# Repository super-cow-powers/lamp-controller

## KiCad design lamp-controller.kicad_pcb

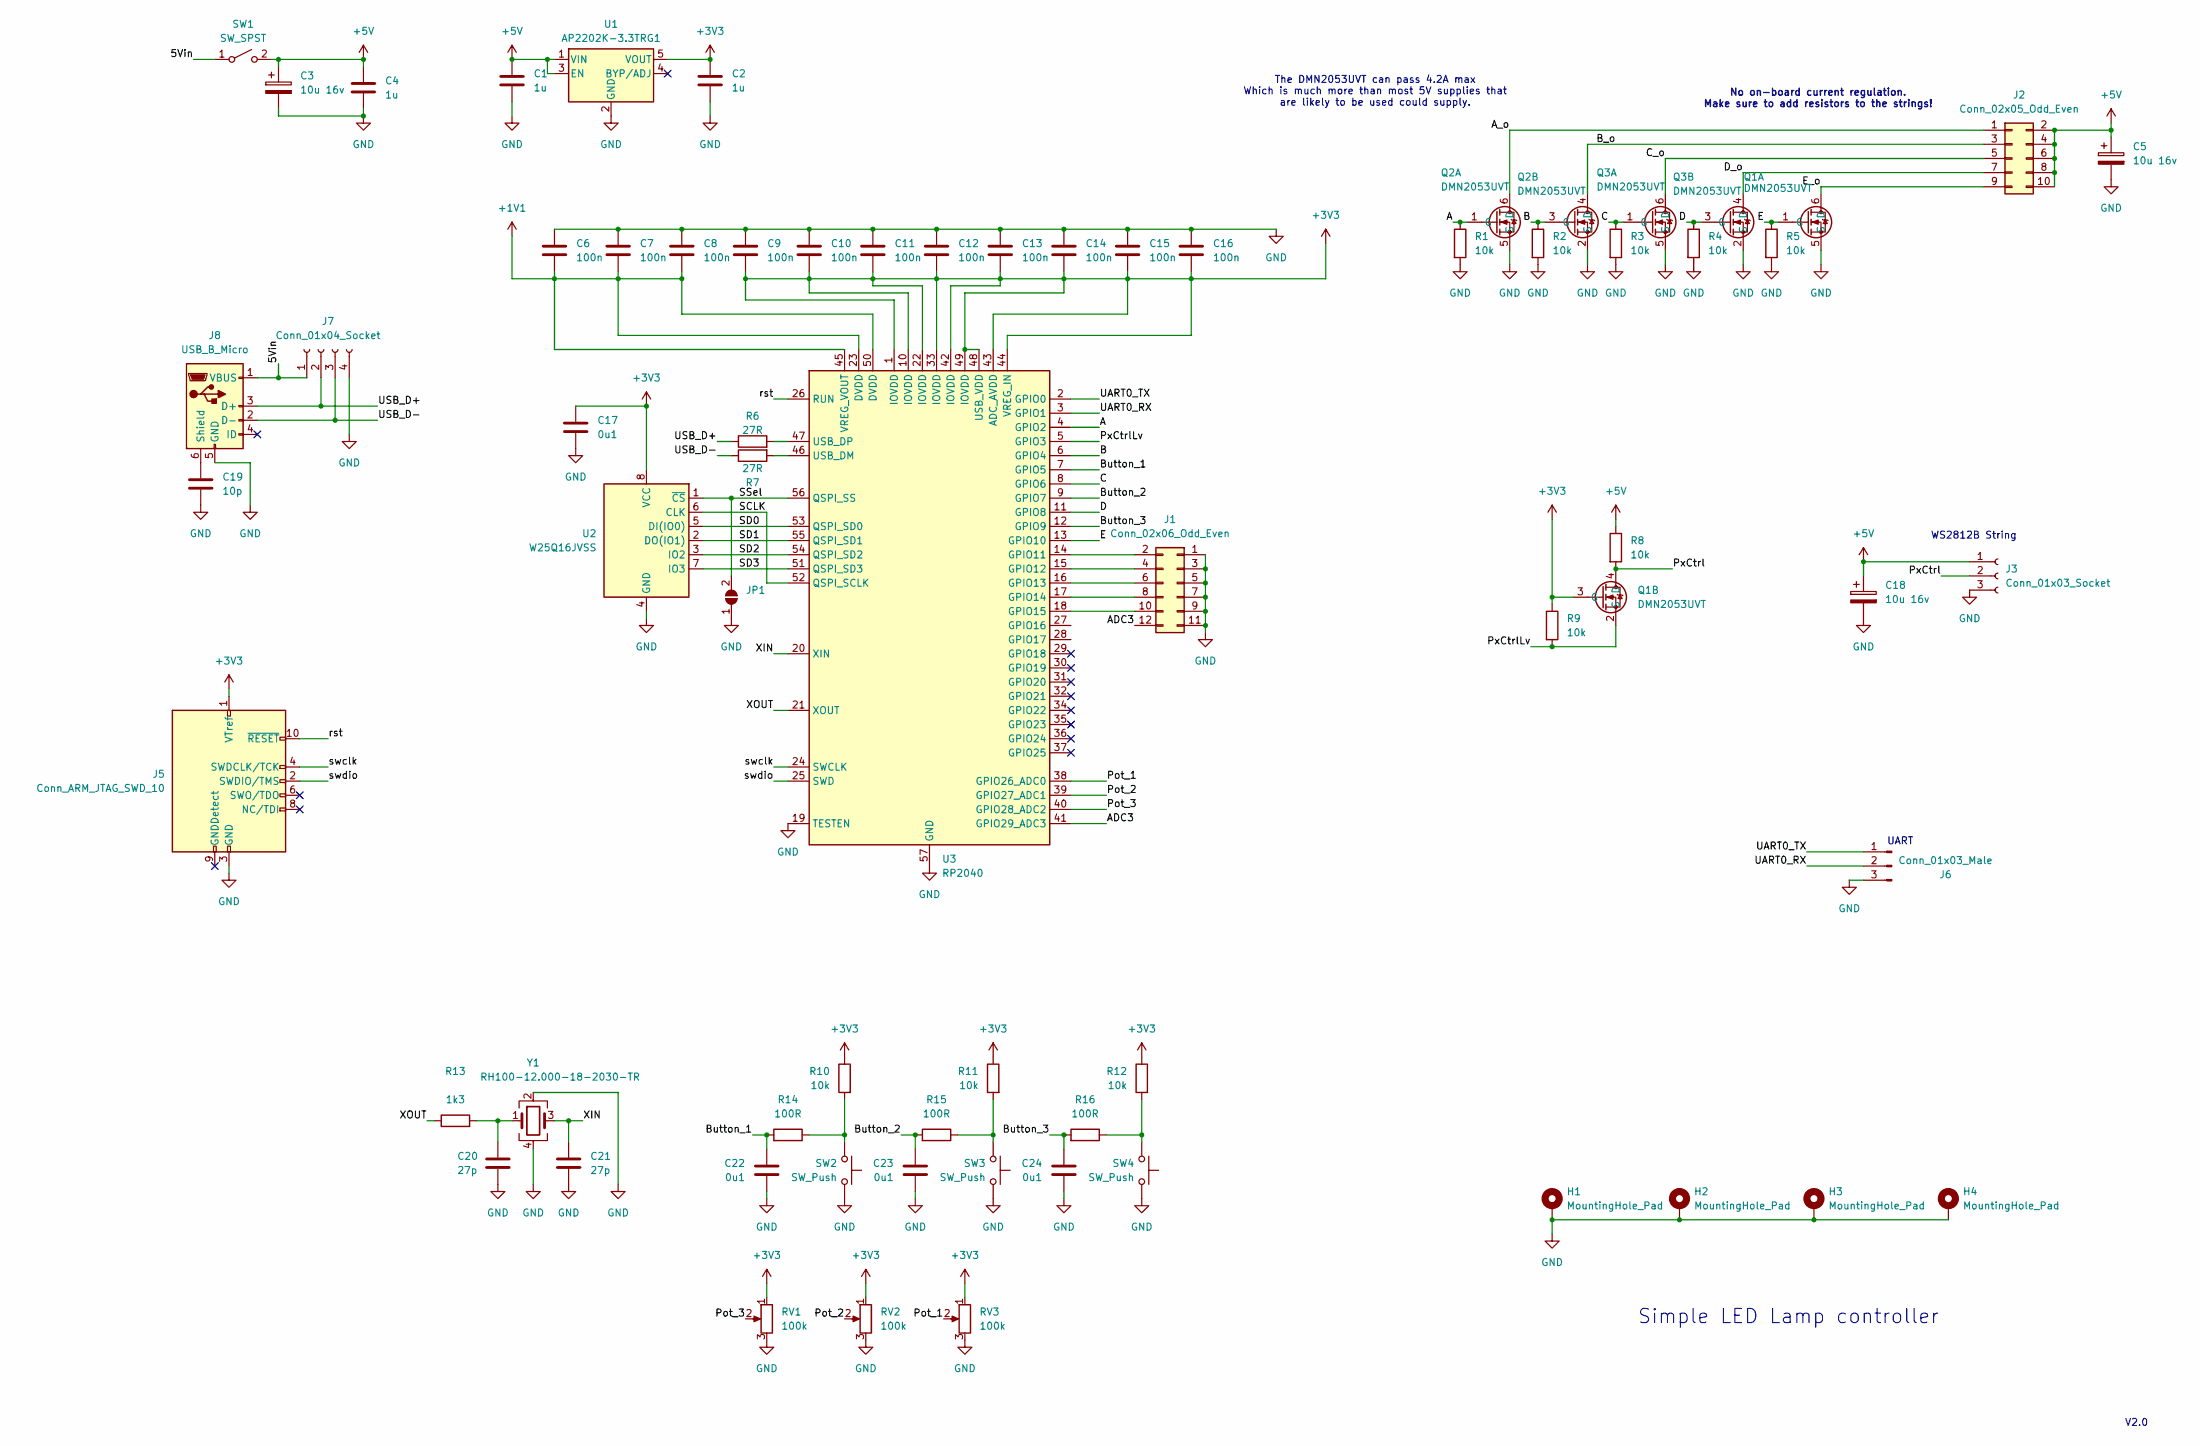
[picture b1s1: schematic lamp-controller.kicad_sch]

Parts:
C1, C2, C4: 1u; C_0603_1608Metric_Pad1.08x0.95mm_HandSolder
C3, C5, C18: 10u 16v; CP_Radial_D4.0mm_P2.00mm
C6, C7, C8, C9, C10, C11, C12, C13, C14, C15, C16: 100n; C_0603_1608Metric_Pad1.08x0.95mm_HandSolder
C17, C22, C23, C24: 0u1; C_0603_1608Metric_Pad1.08x0.95mm_HandSolder
C19: 10p; C_0603_1608Metric_Pad1.08x0.95mm_HandSolder
C20, C21: 27p; C_0603_1608Metric_Pad1.08x0.95mm_HandSolder
H1, H2, H3, H4: MountingHole_Pad; MountingHole_2.2mm_M2_DIN965_Pad
J1: Conn_02x06_Odd_Even; PinHeader_2x06_P2.00mm_Vertical
J2: Conn_02x05_Odd_Even; PinHeader_2x05_P2.54mm_Vertical
J3: Conn_01x03_Socket; PinHeader_1x03_P2.54mm_Vertical
J5: Conn_ARM_JTAG_SWD_10; PinHeader_2x05_P1.27mm_Vertical
J6: Conn_01x03_Male; PinHeader_1x03_P1.00mm_Vertical
J7: Conn_01x04_Socket; PinHeader_1x04_P2.54mm_Vertical
J8: USB_B_Micro; USB_Micro-B_Amphenol_10103594-0001LF_Horizontal
JP1: SolderJumper_2_Open; SolderJumper-2_P1.3mm_Open_RoundedPad1.0x1.5mm
Q1, Q2, Q3: DMN2053UVT; TSOT-23-6
R1, R2, R3, R4, R5, R8, R9, R10, R11, R12: 10k; R_0603_1608Metric_Pad0.98x0.95mm_HandSolder
R6, R7: 27R; R_0603_1608Metric_Pad0.98x0.95mm_HandSolder
R13: 1k3; R_0603_1608Metric_Pad0.98x0.95mm_HandSolder
R14, R15, R16: 100R; R_0603_1608Metric_Pad0.98x0.95mm_HandSolder
RV1, RV2, RV3: 100k; PinHeader_1x03_P1.27mm_Vertical
SW1: SW_SPST; PinHeader_1x02_P2.54mm_Vertical
SW2, SW3, SW4: SW_Push; PinHeader_1x02_P1.27mm_Vertical
U1: AP2202K-3.3TRG1; SOT-23-5
U2: W25Q16JVSS; SOIC-8_5.275x5.275mm_P1.27mm
U3: RP2040; QFN-56-1EP_7x7mm_P0.4mm_EP3.2x3.2mm
Y1: RH100-12.000-18-2030-TR; Crystal_SMD_3225-4Pin_3.2x2.5mm

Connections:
+1V1: C6.2, C7.2, C8.2, U3.23 (DVDD), U3.45 (VREG_VOUT), U3.50 (DVDD)
+3V3: C2.1, C9.2, C10.2, C11.2, C12.2, C13.2, C14.2, C15.2, C16.2, C17.1, J5.1 (VTref), Q1.3 (G), R9.1, R10.1, R11.1, R12.1, RV1.1, RV2.1, RV3.1, U1.5 (VOUT), U2.8 (VCC), U3.1 (IOVDD), U3.10 (IOVDD), U3.22 (IOVDD), U3.33 (IOVDD), U3.42 (IOVDD), U3.43 (ADC_AVDD), U3.44 (VREG_IN), U3.48 (USB_VDD), U3.49 (IOVDD)
+5V: C1.1, C3.1, C4.1, C5.1, C18.1, J2.2, J2.4, J2.6, J2.8, J2.10, J3.1, R8.1, SW1.2 (B), U1.1 (VIN), U1.3 (EN)
/5Vin: J7.1, J8.1 (VBUS), SW1.1 (A)
/A: Q2.1 (G), R1.1, U3.4 (GPIO2)
/ADC3: J1.12, U3.41 (GPIO29_ADC3)
/A_o: J2.1, Q2.6 (D)
/B: Q2.3 (G), R2.1, U3.6 (GPIO4)
/B_o: J2.3, Q2.4 (D)
/Button_1: C22.1, R14.2, U3.7 (GPIO5)
/Button_2: C23.1, R15.2, U3.9 (GPIO7)
/Button_3: C24.1, R16.2, U3.12 (GPIO9)
/C: Q3.1 (G), R3.1, U3.8 (GPIO6)
/C_o: J2.5, Q3.6 (D)
/D: Q3.3 (G), R4.1, U3.11 (GPIO8)
/D_o: J2.7, Q3.4 (D)
/E: Q1.1 (G), R5.1, U3.13 (GPIO10)
/E_o: J2.9, Q1.6 (D)
/Pot_1: RV3.2, U3.38 (GPIO26_ADC0)
/Pot_2: RV2.2, U3.39 (GPIO27_ADC1)
/Pot_3: RV1.2, U3.40 (GPIO28_ADC2)
/PxCtrl: J3.2, Q1.4 (D), R8.2
/PxCtrlLv: Q1.2 (S), R9.2, U3.5 (GPIO3)
/SCLK: U2.6 (CLK), U3.52 (QSPI_SCLK)
/SD0: U2.5 (DI(IO0)), U3.53 (QSPI_SD0)
/SD1: U2.2 (DO(IO1)), U3.55 (QSPI_SD1)
/SD2: U2.3 (IO2), U3.54 (QSPI_SD2)
/SD3: U2.7 (IO3), U3.51 (QSPI_SD3)
/SSel: JP1.2 (B), U2.1 (~CS), U3.56 (QSPI_SS)
/UART0_RX: J6.2, U3.3 (GPIO1)
/UART0_TX: J6.1, U3.2 (GPIO0)
/USB_D+: J7.2, J8.3 (D+), R6.1
/USB_D-: J7.3, J8.2 (D-), R7.1
/XIN: C21.1, U3.20 (XIN), Y1.3
/XOUT: R13.1, U3.21 (XOUT)
/rst: J5.10 (~RESET), U3.26 (RUN)
/swclk: J5.4 (SWDCLK/TCK), U3.24 (SWCLK)
/swdio: J5.2 (SWDIO/TMS), U3.25 (SWD)
GND: C1.2, C2.2, C3.2, C4.2, C5.2, C6.1, C7.1, C8.1, C9.1, C10.1, C11.1, C12.1, C13.1, C14.1, C15.1, C16.1, C17.2, C18.2, C19.2, C20.2, C21.2, C22.2, C23.2, C24.2, H1.1, H2.1, H3.1, H4.1, J1.1, J1.3, J1.5, J1.7, J1.9, J1.11, J3.3, J5.3 (GND), J5.5 (GND), J6.3, J7.4, J8.5 (GND), JP1.1 (A), Q1.5 (S), Q2.2 (S), Q2.5 (S), Q3.2 (S), Q3.5 (S), R1.2, R2.2, R3.2, R4.2, R5.2, RV1.3, RV2.3, RV3.3, SW2.1, SW3.1, SW4.1, U1.2 (GND), U2.4 (GND), U3.19 (TESTEN), U3.57 (GND), Y1.2, Y1.4
unnamed: C20.1, R13.2, Y1.1
unnamed: J1.2, U3.14 (GPIO11)
unnamed: J1.4, U3.15 (GPIO12)
unnamed: J1.6, U3.16 (GPIO13)
unnamed: J1.8, U3.17 (GPIO14)
unnamed: J1.10, U3.18 (GPIO15)
unnamed: C19.1, J8.6 (Shield)
unnamed: R10.2, R14.1, SW2.2
unnamed: R11.2, R15.1, SW3.2
unnamed: R12.2, R16.1, SW4.2
unnamed: R7.2, U3.46 (USB_DM)
unnamed: R6.2, U3.47 (USB_DP)

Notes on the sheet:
The DMN2053UVT can pass 4.2A max Which is much more than most 5V supplies that are likely to be used could supply.
UART
No on-board current regulation. Make sure to add resistors to the strings!
Simple LED Lamp controller
V2.0
WS2812B String

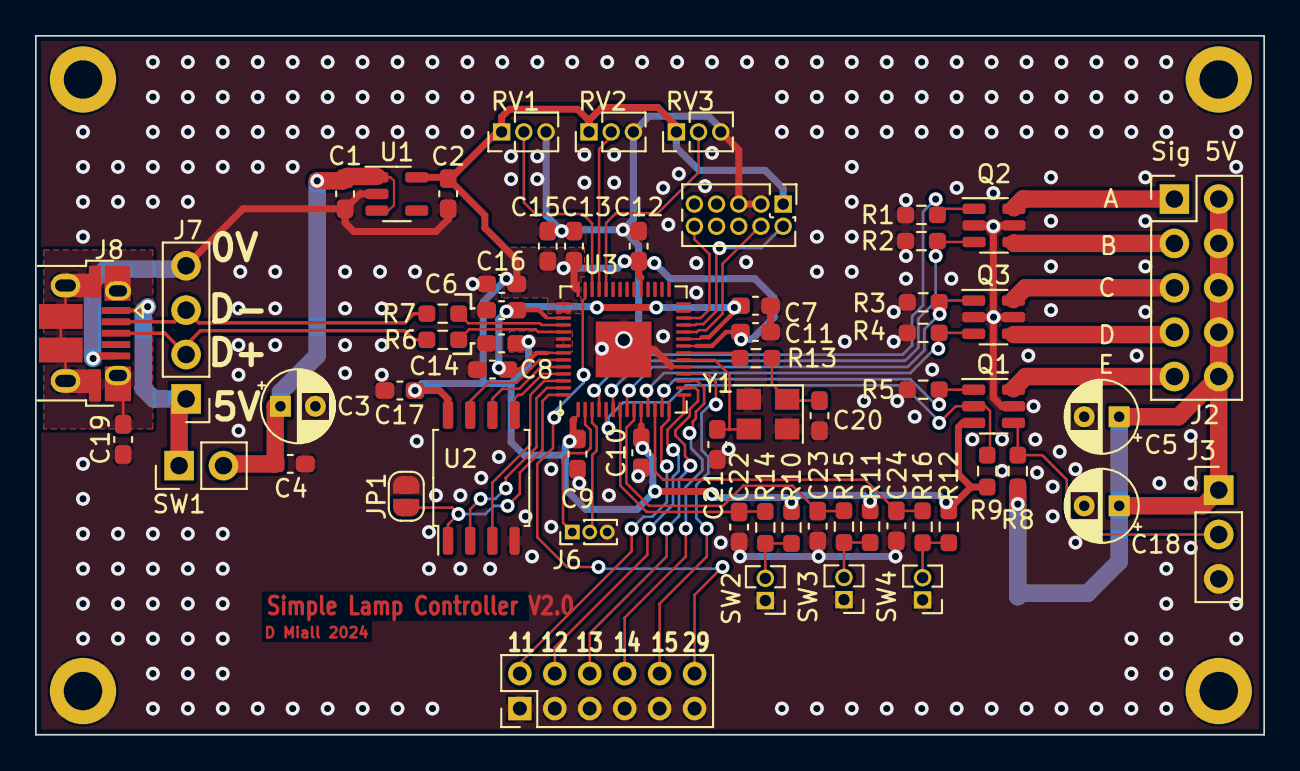
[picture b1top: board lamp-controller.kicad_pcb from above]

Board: 2 copper layers, 70.3 x 40.0 mm, 66 parts (0 on the bottom side), 51 nets.

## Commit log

2023-12-16 Init
2023-12-17 Layout
2023-12-17 Add fab outputs
2024-01-06 RP2040 Version
